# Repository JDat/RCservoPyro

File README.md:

# RCservoPyro
Converts from RC servo input to ON/OFF for pyro charge or ON/OFF switch

This project read input from one RC servo channel and turns on output. Useful for ON/OFF control from RC. Have Normal Open or Normal Closed version (depending on soldered components). Additional Status LED for pyro charge continuity check.

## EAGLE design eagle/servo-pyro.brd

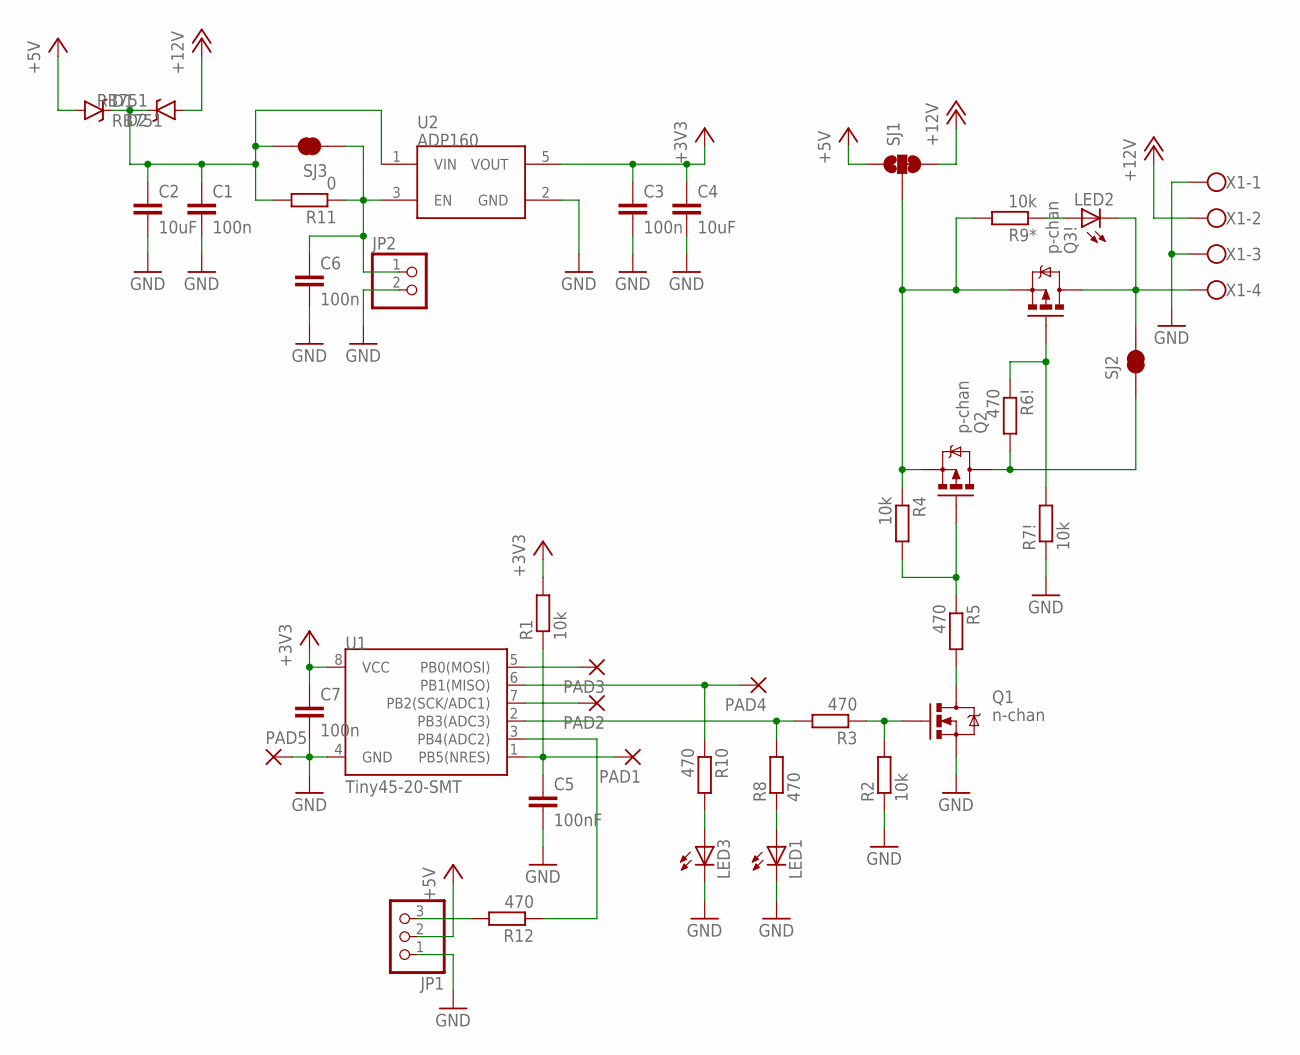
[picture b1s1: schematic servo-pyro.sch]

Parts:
C1, C3, C6, C7: 100n; C0603K
C2, C4: 10uF; C0603K
C5: 100nF; C0603K
D1, D2: RB751; SOD-523
JP1: PINHD-1X3; 1X03
JP2: PINHD-1X2; 1X02
LED1, LED2, LED3: LEDCHIPLED_0603; CHIPLED_0603
PAD1, PAD2, PAD3, PAD4, PAD5: 1,6/0,8
Q1: n-chan; SOT23-3
Q2, Q3!: p-chan; SOT23-3
R1, R2, R4, R7!, R9*: 10k; R0603
R3, R5, R6!, R8, R10, R12: 470; R0603
R11: 0; R0603
SJ1: JUMPER-PAD-3-2OF3_NC_BY_TRACE_LARGE; PAD-JUMPER-3-2OF3_NC_BY_TRACE_YES_SILK_LARGE
SJ2, SJ3: JUMPER-PAD-2-NC_BY_TRACENO_SILK; PAD-JUMPER-2-NC_BY_TRACE_NO_SILK
U1: Tiny45-20-SMT; SO08-EIAJ
U2: ADP160; SOT23-5
X1: W237-4

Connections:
+3V3: C3.1, C4.1, C7.1, R1.2, U1.8 (VCC), U2.5 (VOUT)
+5V: D1.A, JP1.2, SJ1.1
+12V: D2.A, SJ1.3, X1.2
GND: C1.2, C2.2, C3.2, C4.2, C5.2, C6.2, C7.2, JP1.1, JP2.2, LED1.C, LED3.C, PAD5.1, Q1.2 (S), R2.1, R7!.1, U1.4 (GND), U2.2 (GND), X1.1, X1.3
unnamed: C5.1, PAD1.1, R1.1, U1.1 (PB5(NRES))
unnamed: C6.1, JP2.1, R11.1, SJ3.1, U2.3 (EN)
unnamed: LED2.A, R9*.1
unnamed: C1.1, C2.1, D1.C, D2.C, R11.2, SJ3.2, U2.1 (VIN)
unnamed: PAD2.1, U1.7 (PB2(SCK/ADC1))
unnamed: PAD3.1, U1.5 (PB0(MOSI))
unnamed: Q3!.1 (G), R6!.1, R7!.2
unnamed: Q2.1 (G), R4.2, R5.1
unnamed: Q1.1 (G), R2.2, R3.1
unnamed: Q1.3 (D), R5.2
unnamed: LED1.A, R8.1
unnamed: R3.2, R8.2, U1.2 (PB3(ADC3))
unnamed: LED3.A, R10.2
unnamed: JP1.3, R12.2
unnamed: R12.1, U1.3 (PB4(ADC2))
unnamed: PAD4.1, R10.1, U1.6 (PB1(MISO))
PWR_IN: Q2.2 (S), Q3!.2 (S), R4.1, R9*.2, SJ1.2
PWR_ON: Q2.3 (D), R6!.2, SJ2.1
PWR_OUT: LED2.C, Q3!.3 (D), SJ2.2, X1.4

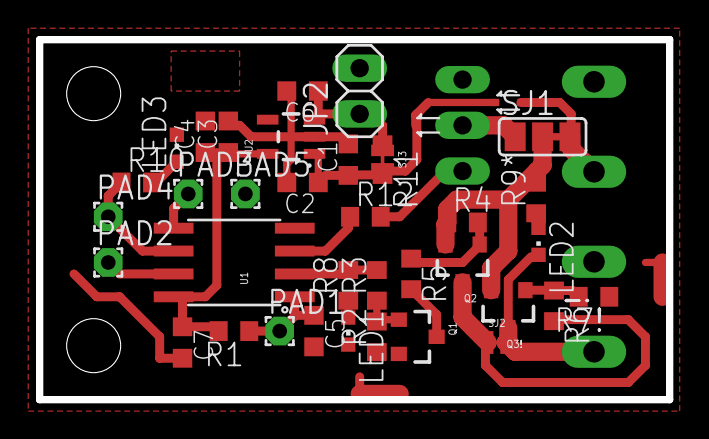
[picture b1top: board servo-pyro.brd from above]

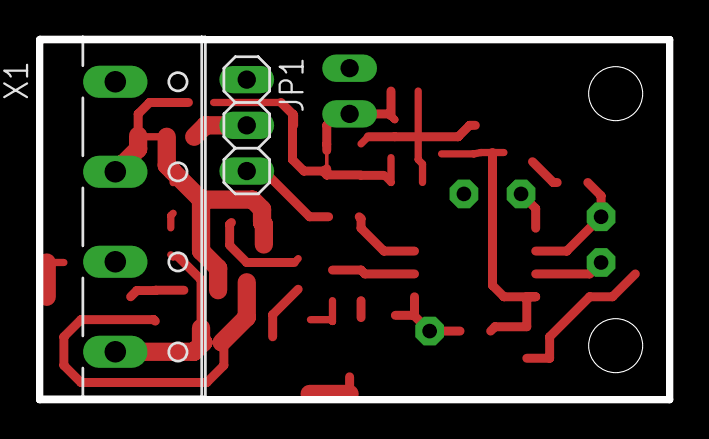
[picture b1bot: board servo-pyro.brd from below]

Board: 2 copper layers, 35.0 x 20.0 mm, 40 parts (2 on the bottom side), 23 nets.

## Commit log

2017-10-03 added arduino

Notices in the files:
parts and their libraries:
SparkFun-DiscreteSemi: Licensing: Creative Commons ShareAlike 4.0 International - https://creativecommons.org/licenses/by-sa/4.0
